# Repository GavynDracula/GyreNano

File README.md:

# Gyre Nano · 洄流

**English** | [简体中文](README.zh-CN.md)

A wireless, hot-swap split trackball keyboard enclosure derived from [BastardKB Charybdis Nano](https://github.com/Bastardkb/Charybdis). It keeps the familiar 3×5 keywell and thumb layout while replacing the open frame with a rounded, closed enclosure inspired by Charybdis MK2.

“Gyre / 洄流” echoes the swirling water of Charybdis; Nano denotes the compact layout. This is an independent derivative project.

**Current enclosure prototype: integrated raised shoulders and a rounded forward ball collar.** The latest upper shells preserve the original key/thumb/ball mounting relationships and reuse the existing bottom trays and FR4/FPC supports. Geometry and assembly-clearance checks have passed; these shells have not been sliced or physically assembled. Images show the current model.

[Latest models and checks](models/raised-rim/README.md) · [Ball-collar close-up](models/raised-rim/right-outer-seam.png) · [Top view](models/raised-rim/top.png)

## Layout and compatibility

- 3×5 main keys per half; three left thumb keys, two right thumb keys and a 34 mm trackball: 35 keys total.
- **Mounting positions and relative axes of the main keys, thumb keys and original trackball seat are preserved.** Baselines are mirrored Skeletyl V4 `case_v4_103.stl` on the left and Charybdis Nano `charybdisnano_v2_v187.stl` on the right. [Verification details](docs/geometry.md)
- The outer skin, thumb/ball transitions, sidewalls and bottom trays are redesigned. Height above the desk is not claimed identical to the original.
- Current electronics routes use FR4 or FPC keyfields, Kailh hot-swap sockets, header-mounted nrfmicro and ZMK. The original prototype used Amoeba Royale single-switch PCBs and Elite-C-holder; the new holder and support designs are linked below.
- Original holder mounting datums, a Type-C opening and bottom screw bosses adjacent to the sidewalls.
- Dedicated battery accommodation and a nice!view window remain planned. Ready-to-flash firmware is not included; the prototype PCB designs are linked below.

## Required prints

Print files are in [`models/`](models/) as **geometry-only 3MF**, in millimetres. Import at **100% scale** using your own printer profile; no printer settings or G-code are embedded. The left case is already mirrored.

| Part | File |
| --- | --- |
| Current right upper shell | [GyreNanoRightShell.3mf](models/raised-rim/GyreNanoRightShell.3mf) |
| Current left upper shell | [GyreNanoLeftShell.3mf](models/raised-rim/GyreNanoLeftShell.3mf) |
| Right bottom V7 | [gyre-nano-right-bottom-v7.3mf](models/3x5/gyre-nano-right-bottom-v7.3mf) |
| Left bottom V7 | [gyre-nano-left-bottom-v7.3mf](models/3x5/gyre-nano-left-bottom-v7.3mf) |
| FR4 supports, if using FR4 | [Main and thumb retainers](models/integrated-fr4/README.md) |
| FPC supports, if using FPC | [Direct supports and fit coupons](models/fpc-supports/README.md) |

Bottom STEP files are also in [`models/3x5/`](models/3x5/), in assembly coordinates; bottom 3MF files use bed coordinates. Upper cases are mesh models, without exact B-rep STEP exports.

Choose one support set for your PCB route. The earlier [V11/V7 shells](models/3x5/) and [V14 integrated shells](models/integrated-fr4/README.md) remain available as references. The current 3MFs preserve the checked STL coordinates and triangles exactly; large ASCII STL viewing copies remain local and are excluded from Git.

Use the original upstream trackball components below. Their final installed positions have been checked for static fit:

| Part | Charybdis file |
| --- | --- |
| Nano adapter top | [`adapter_v2_top_v75.stl`](https://github.com/Bastardkb/Charybdis/blob/47af70b9cd9b8d1d3a055ea88ab95c724bd3c02a/files/3x5%20nano/adapter_v2_top_v75.stl) |
| BTU adapter bottom | [`adapter_btu_bottom_v32.stl`](https://github.com/Bastardkb/Charybdis/blob/47af70b9cd9b8d1d3a055ea88ab95c724bd3c02a/files/mods/btu/adapter_btu_bottom_v32.stl) |
| Sensor cover | [`sensor_cover_v51.stl`](https://github.com/Bastardkb/Charybdis/blob/47af70b9cd9b8d1d3a055ea88ab95c724bd3c02a/files/sensor_cover_v51.stl) |

## FDM printing and assembly

Target trial printer: Creality K1C, 0.4 mm nozzle, PLA/PETG. Slice the current models using your own profile. Start with the support fit coupons for your PCB route; the [earlier holder/USB and ball/thumb samples](models/trials/) can check inherited interfaces but do not reproduce the new shoulder or collar. Keycap travel, tool access, adapter installation motion, support removal and manufacturing tolerances still need physical trials. Local thin features inherited from the ball opening are documented in the [current checks](models/raised-rim/README.md).

[FDM printing notes](docs/printing.md) · [Geometry checks and limits](docs/geometry.md) · [Build guide (TBD)](docs/build-guide.md)

## Electronics and integrated prints

**Electronics baseline: v0.2.0-prototype.1 — waiting for PCB samples and physical assembly.** The current enclosure update adds no PCB changes. Both column-PCB routes can use the latest upper shells with their matching supports; the earlier release archives retain their original models.

| Route / part | Files |
| --- | --- |
| FR4 keyfield, 0.6 mm, 99.70 × 99.80 mm | [V33 KiCad / EDA / Gerber](pcb/keyfield-fr4/README.md) |
| Retained electrically isolated FR4 alternative | [V32](pcb/keyfield-fr4/alternative-isolated/README.md) |
| FPC keyfield, 0.11 mm, 97.18 × 96.47 mm | [V27 KiCad / sample Gerber](pcb/keyfield-fpc/README.md) |
| Left/right controller holders | [Corrected native EDA projects](pcb/holders/README.md) |
| PMW3610 sensor with FFC | [Corrected native EDA project](pcb/sensor/README.md) |
| Current upper shells | [3MF / previews / checks](models/raised-rim/README.md) |
| Matching FR4 retainers and V14 reference shells | [STL / STEP](models/integrated-fr4/README.md) |
| Bare-FPC direct supports | [STL / 3MF / STEP](models/fpc-supports/README.md) |

Existing holder interfaces and key/ball mounting poses are retained. Six keyfield FFCs are still required per hand. Cross-region FR4 bridges must be removed before curved installation. Thin-FR4 forming, FPC durability, complete cable paths and printed fit remain trial items. No 0.4 mm thickness change is included.

[Electronics index](pcb/README.md) · [BOM](pcb/keyfield-fpc/BOM.zh-CN.md) · [CSV](pcb/keyfield-fpc/BOM.csv) · [All prints](models/README.md) · [Firmware placeholder](docs/firmware.md)

## Repository layout

| Path | Contents |
| --- | --- |
| `models/` | Print-ready geometry, integrated shells and FR4/FPC retainers |
| `pcb/` | Current KiCad/EDA projects, sample packages, BOM and checks |
| `docs/` | Build/printing notes, images, verification and release records |
| `development/` | Modeling sources, dimensions, reference geometry and engineering tools |

See [development notes](docs/DEVELOPMENT.md) for dependencies and coordinate conventions. Old cross-version pipelines are preserved as a checksummed engineering snapshot attached to the pre-release; disposable exports and local caches are excluded from Git.

## Attribution and license

Mechanical designs derive from [Charybdis](https://github.com/Bastardkb/Charybdis) and [Skeletyl](https://github.com/Bastardkb/Skeletyl) by BastardKB and their original contributors, under **CC BY-NC-SA 4.0**. Changes here include the closed skin, blended transitions, wireless hardware accommodation and matching bottom trays.

[Elite-C-holder](https://github.com/Bastardkb/Elite-C-holder), [Amoeba Royale](https://github.com/mtl/keyboard-pcbs/tree/master/amoeba-royale) and [ZMK](https://github.com/zmkfirmware/zmk) retain their respective authorship and licenses. See [license scope](LICENSE.md) and [source records](docs/ATTRIBUTION.md).

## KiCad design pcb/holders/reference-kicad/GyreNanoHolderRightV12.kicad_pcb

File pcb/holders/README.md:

# Left / right holders

The current editable designs are the corrected native JLCEDA V22 projects:

- [Left holder](eda/GyreNanoHolderLeft/GyreNanoHolderLeft.eprj3).
- [Right holder](eda/GyreNanoHolderRight/GyreNanoHolderRight.eprj3).

Keep each project folder intact. Each holder has seven 6-pin FFC sockets: J1–J5 main columns, J6 thumb, J7 sensor (unused on the left). The controller/header mounting datums and battery/switch interfaces are retained. Source stack thickness is 1.6 mm; the actual order selections are not independently verified.

[EDA validation and deliberate changes](../eda-validation/README.md) · [BOM](../keyfield-fpc/BOM.zh-CN.md)

`reference-kicad/` contains the original V12 source boards and a local footprint library. **These older boards omit controller PTH solder-mask openings that were corrected in EDA.** They are provenance references, not the recommended reorder source.

中文：左右 holder 用户已打板；当前入口为原生嘉立创 EDA 工程，每侧七个插座。参考 KiCad 版保留原始数据，但旧阻焊开窗问题没有回填，重新下单请使用 EDA 版。项目叠层厚度与实际订单参数应区分。

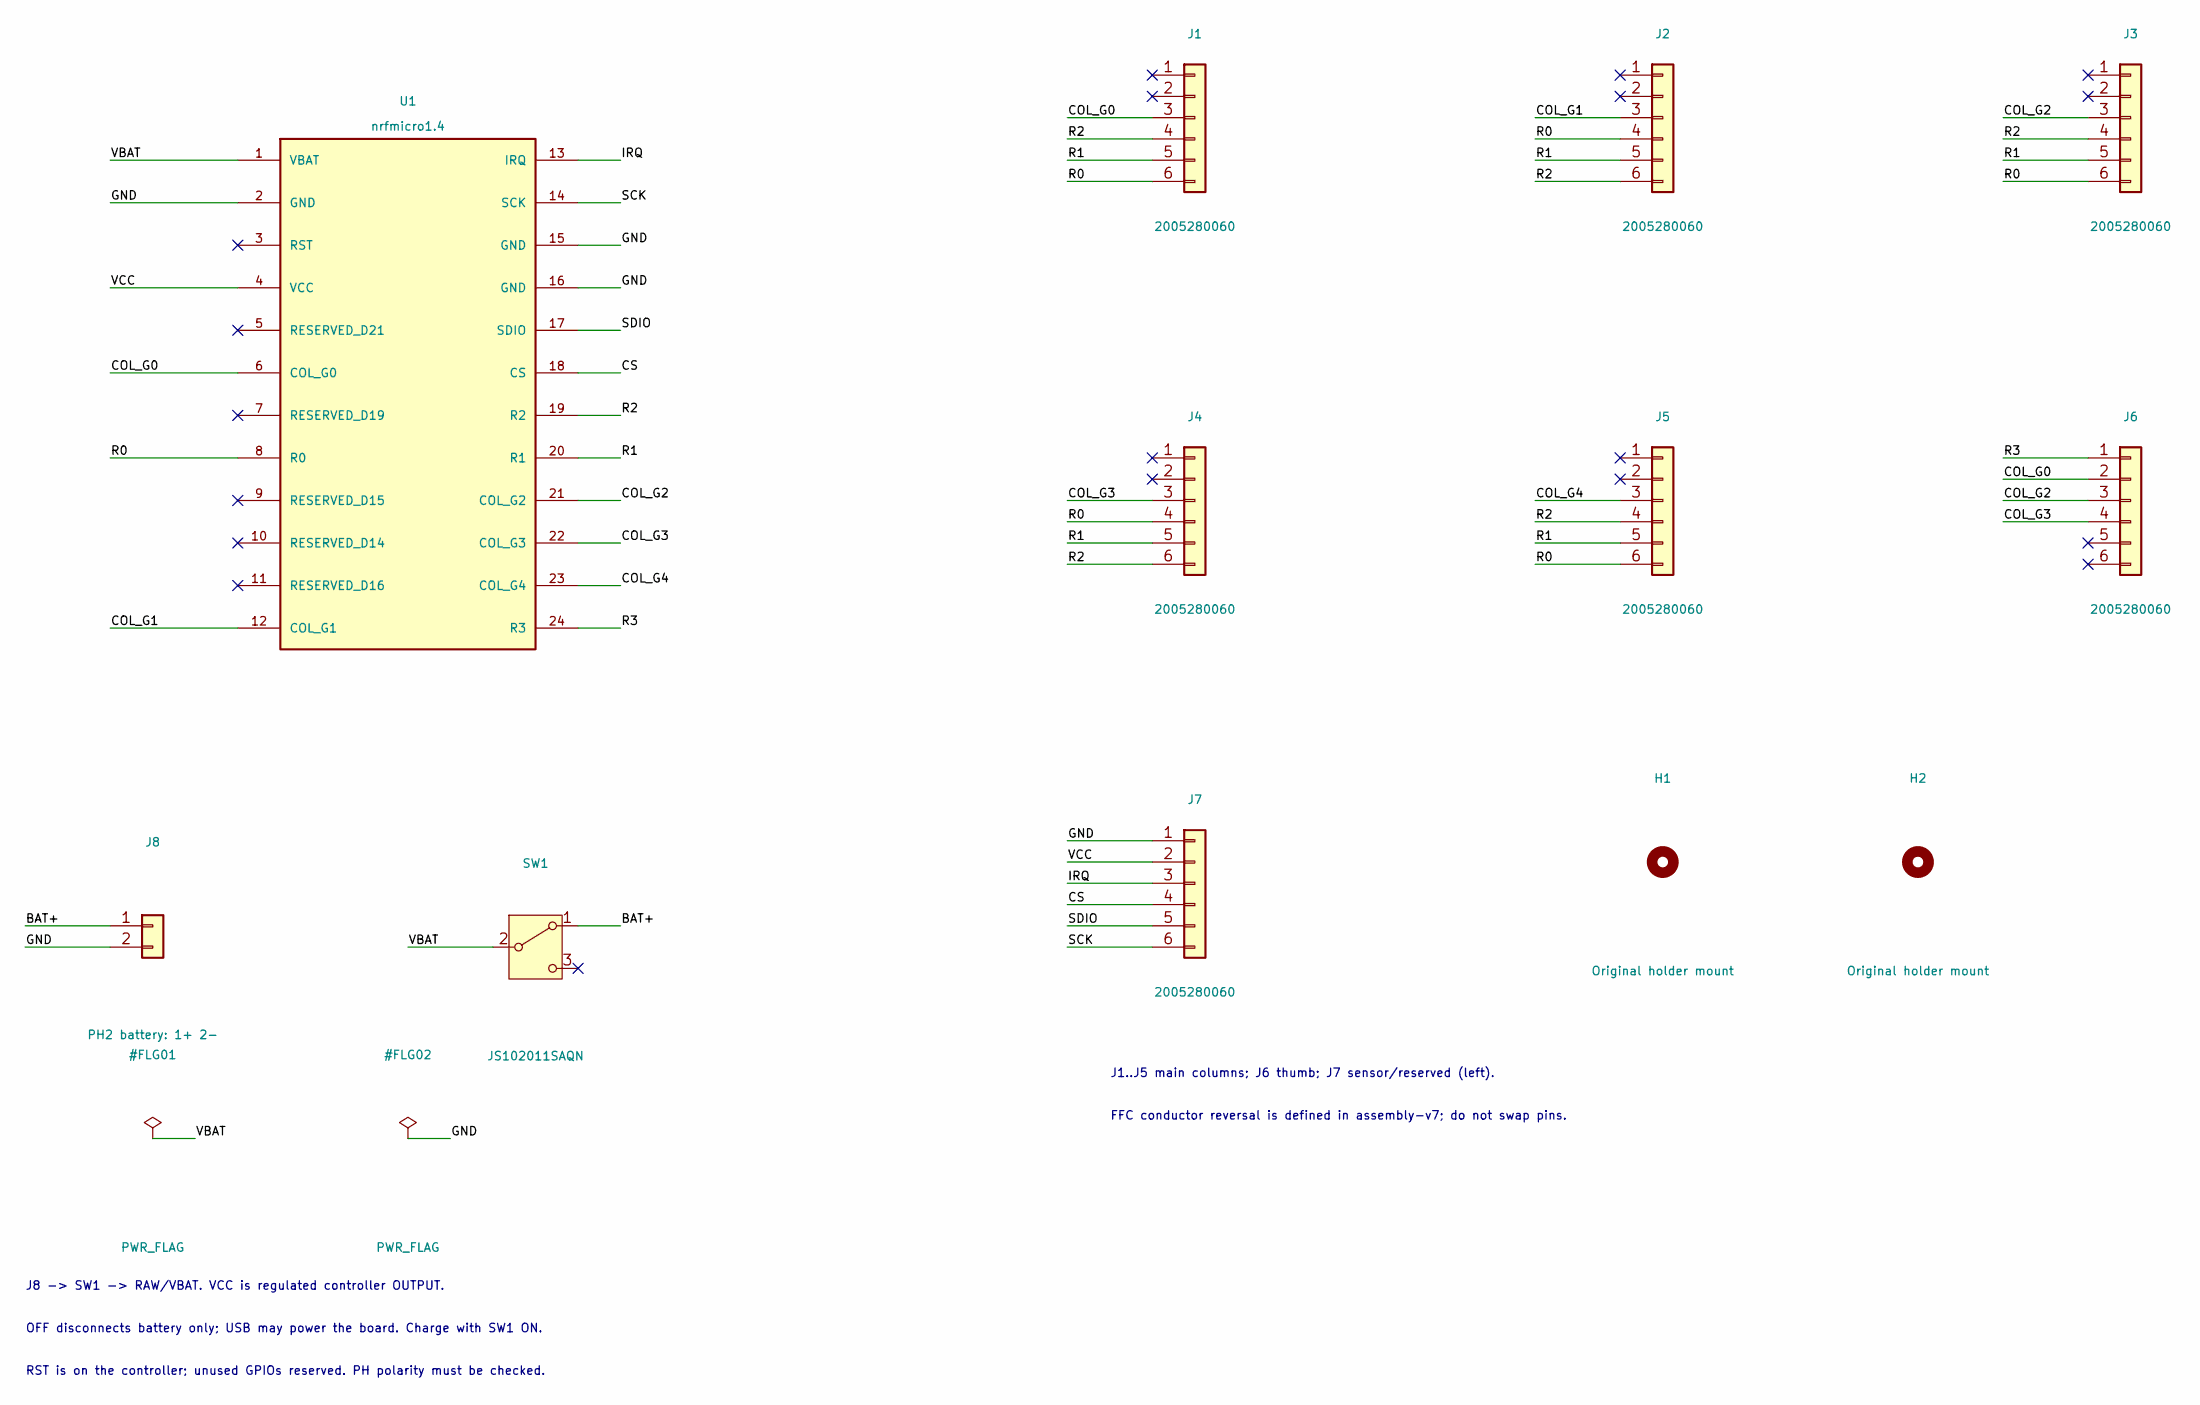
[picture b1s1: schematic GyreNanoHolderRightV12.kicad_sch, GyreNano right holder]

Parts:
H1, H2: Original holder mount; Mount4
J1: 2005280060; FFC6_right_J1
J2: 2005280060; FFC6_right_J2
J3: 2005280060; FFC6_right_J3
J4: 2005280060; FFC6_right_J4
J5: 2005280060; FFC6_right_J5
J6: 2005280060; Molex_200528-0060_1x06-1MP_P1.00mm_Horizontal
J7: 2005280060; FFC6_right_J7
J8: PH2 battery: 1+ 2-; JST_PH_B2B-PH-SM4-TB_1x02-1MP_P2.00mm_Vertical
SW1: JS102011SAQN; SW_SPDT_CK_JS102011SAQN
U1: nrfmicro1.4; Controller24_right

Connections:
/BAT+: J8.1, SW1.1 (A)
/COL_G0: J1.3, J6.2, U1.6 (COL_G0)
/COL_G1: J2.3, U1.12 (COL_G1)
/COL_G2: J3.3, J6.3, U1.21 (COL_G2)
/COL_G3: J4.3, J6.4, U1.22 (COL_G3)
/COL_G4: J5.3, U1.23 (COL_G4)
/CS: J7.4, U1.18 (CS)
/GND: J7.1, J8.2, U1.2 (GND), U1.15 (GND), U1.16 (GND)
/IRQ: J7.3, U1.13 (IRQ)
/R0: J1.6, J2.4, J3.6, J4.4, J5.6, U1.8 (R0)
/R1: J1.5, J2.5, J3.5, J4.5, J5.5, U1.20 (R1)
/R2: J1.4, J2.6, J3.4, J4.6, J5.4, U1.19 (R2)
/R3: J6.1, U1.24 (R3)
/SCK: J7.6, U1.14 (SCK)
/SDIO: J7.5, U1.17 (SDIO)
/VBAT: SW1.2 (B), U1.1 (VBAT)
/VCC: J7.2, U1.4 (VCC)

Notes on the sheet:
J1..J5 main columns; J6 thumb; J7 sensor/reserved (left).
FFC conductor reversal is defined in assembly-v7; do not swap pins.
J8 -> SW1 -> RAW/VBAT. VCC is regulated controller OUTPUT.
OFF disconnects battery only; USB may power the board. Charge with SW1 ON.
RST is on the controller; unused GPIOs reserved. PH polarity must be checked.

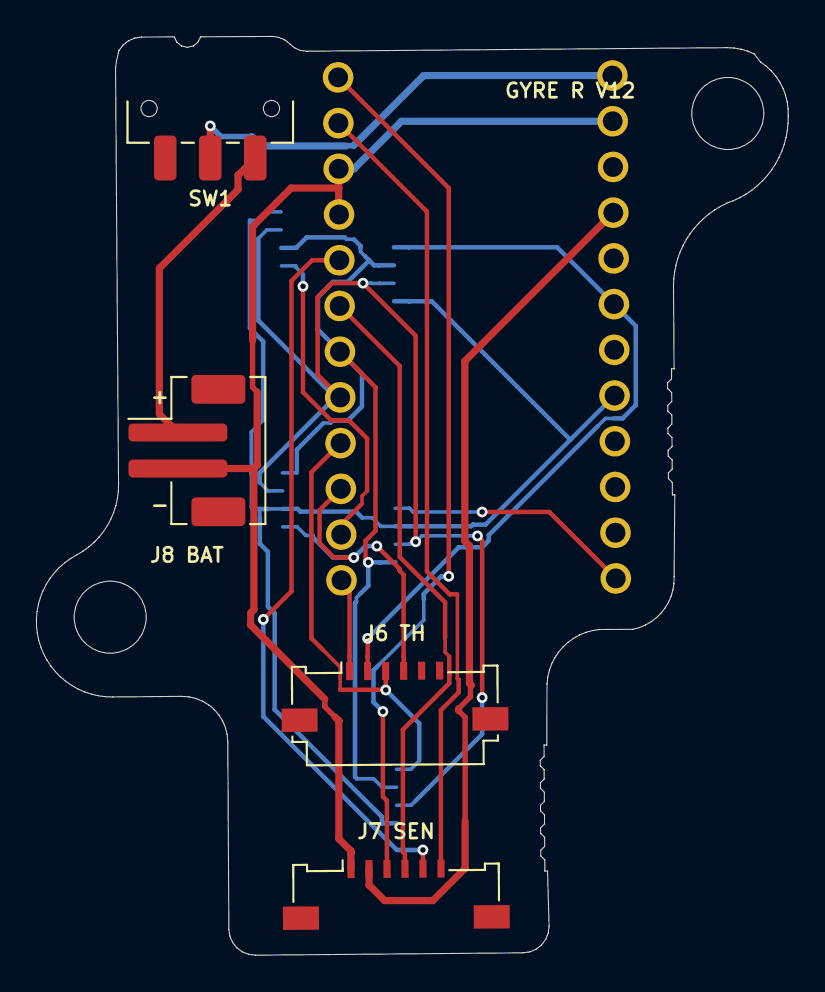
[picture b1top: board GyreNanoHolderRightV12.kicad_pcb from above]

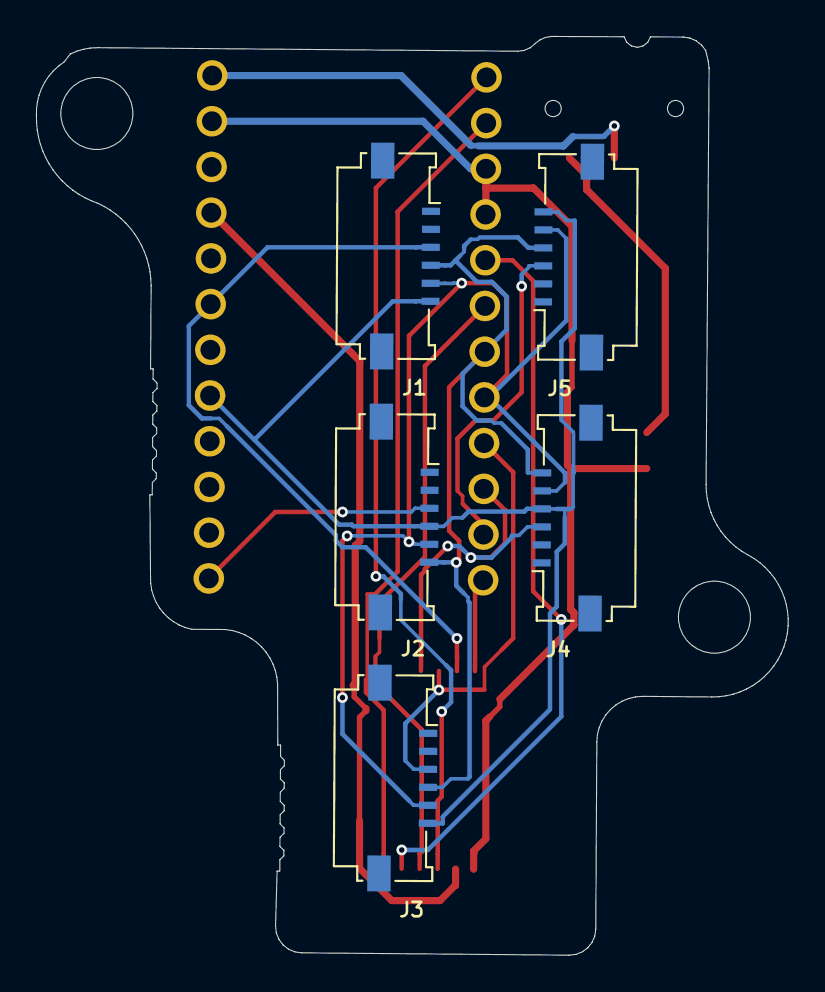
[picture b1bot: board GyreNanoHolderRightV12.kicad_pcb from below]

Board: 2 copper layers, 41.8 x 51.0 mm, 12 parts (5 on the bottom side), 17 nets.

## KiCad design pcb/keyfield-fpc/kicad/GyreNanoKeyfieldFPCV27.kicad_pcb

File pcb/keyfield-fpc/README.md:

# FPC keyfield — V27

[简体中文](README.zh-CN.md)

One common 18-key artwork for both hands; use 18 keys on the left and omit/remove T_SW1/T_D1 for 17 on the right. **97.176 × 96.472 mm**, two-layer **0.11 mm PI FPC**, 1/3 oz copper. Existing holder pin maps and six keyfield FFCs per hand are retained.

[KiCad project](kicad/GyreNanoKeyfieldFPCV27.kicad_pro) · [submitted sample ZIP](fabrication/GyreNanoKeyfieldFPCV27-SampleED.zip) · [sample process notes](SAMPLE-FABRICATION.txt) · [BOM CSV](BOM.csv) · [采购清单](BOM.zh-CN.md)

The sample package requests adhesiveless electrodeposited copper, yellow coverlay, ENIG 1 µin and no factory stiffeners. It is a material/assembly experiment, not a production-qualified specification. The older quotation ZIP remains separately named for traceability.

JP1: bridge 1–2 for left, 2–3 for right; never both. Remove optional inter-region bridges for the screened installation. [DRC/ERC, 64 cut/hand cases, CAM and folded geometry evidence](checks/) is retained unchanged.

The original sample notes describe separately bonded FR4 backers. An alternative [printed direct-support set](../../models/fpc-supports/README.md) is now available; it replaces those backers in its modeled stack. Do not stack both support schemes without a fit review. FPC bending, soldering, hot-swap loads and complete cable/latch assembly remain to be tested.

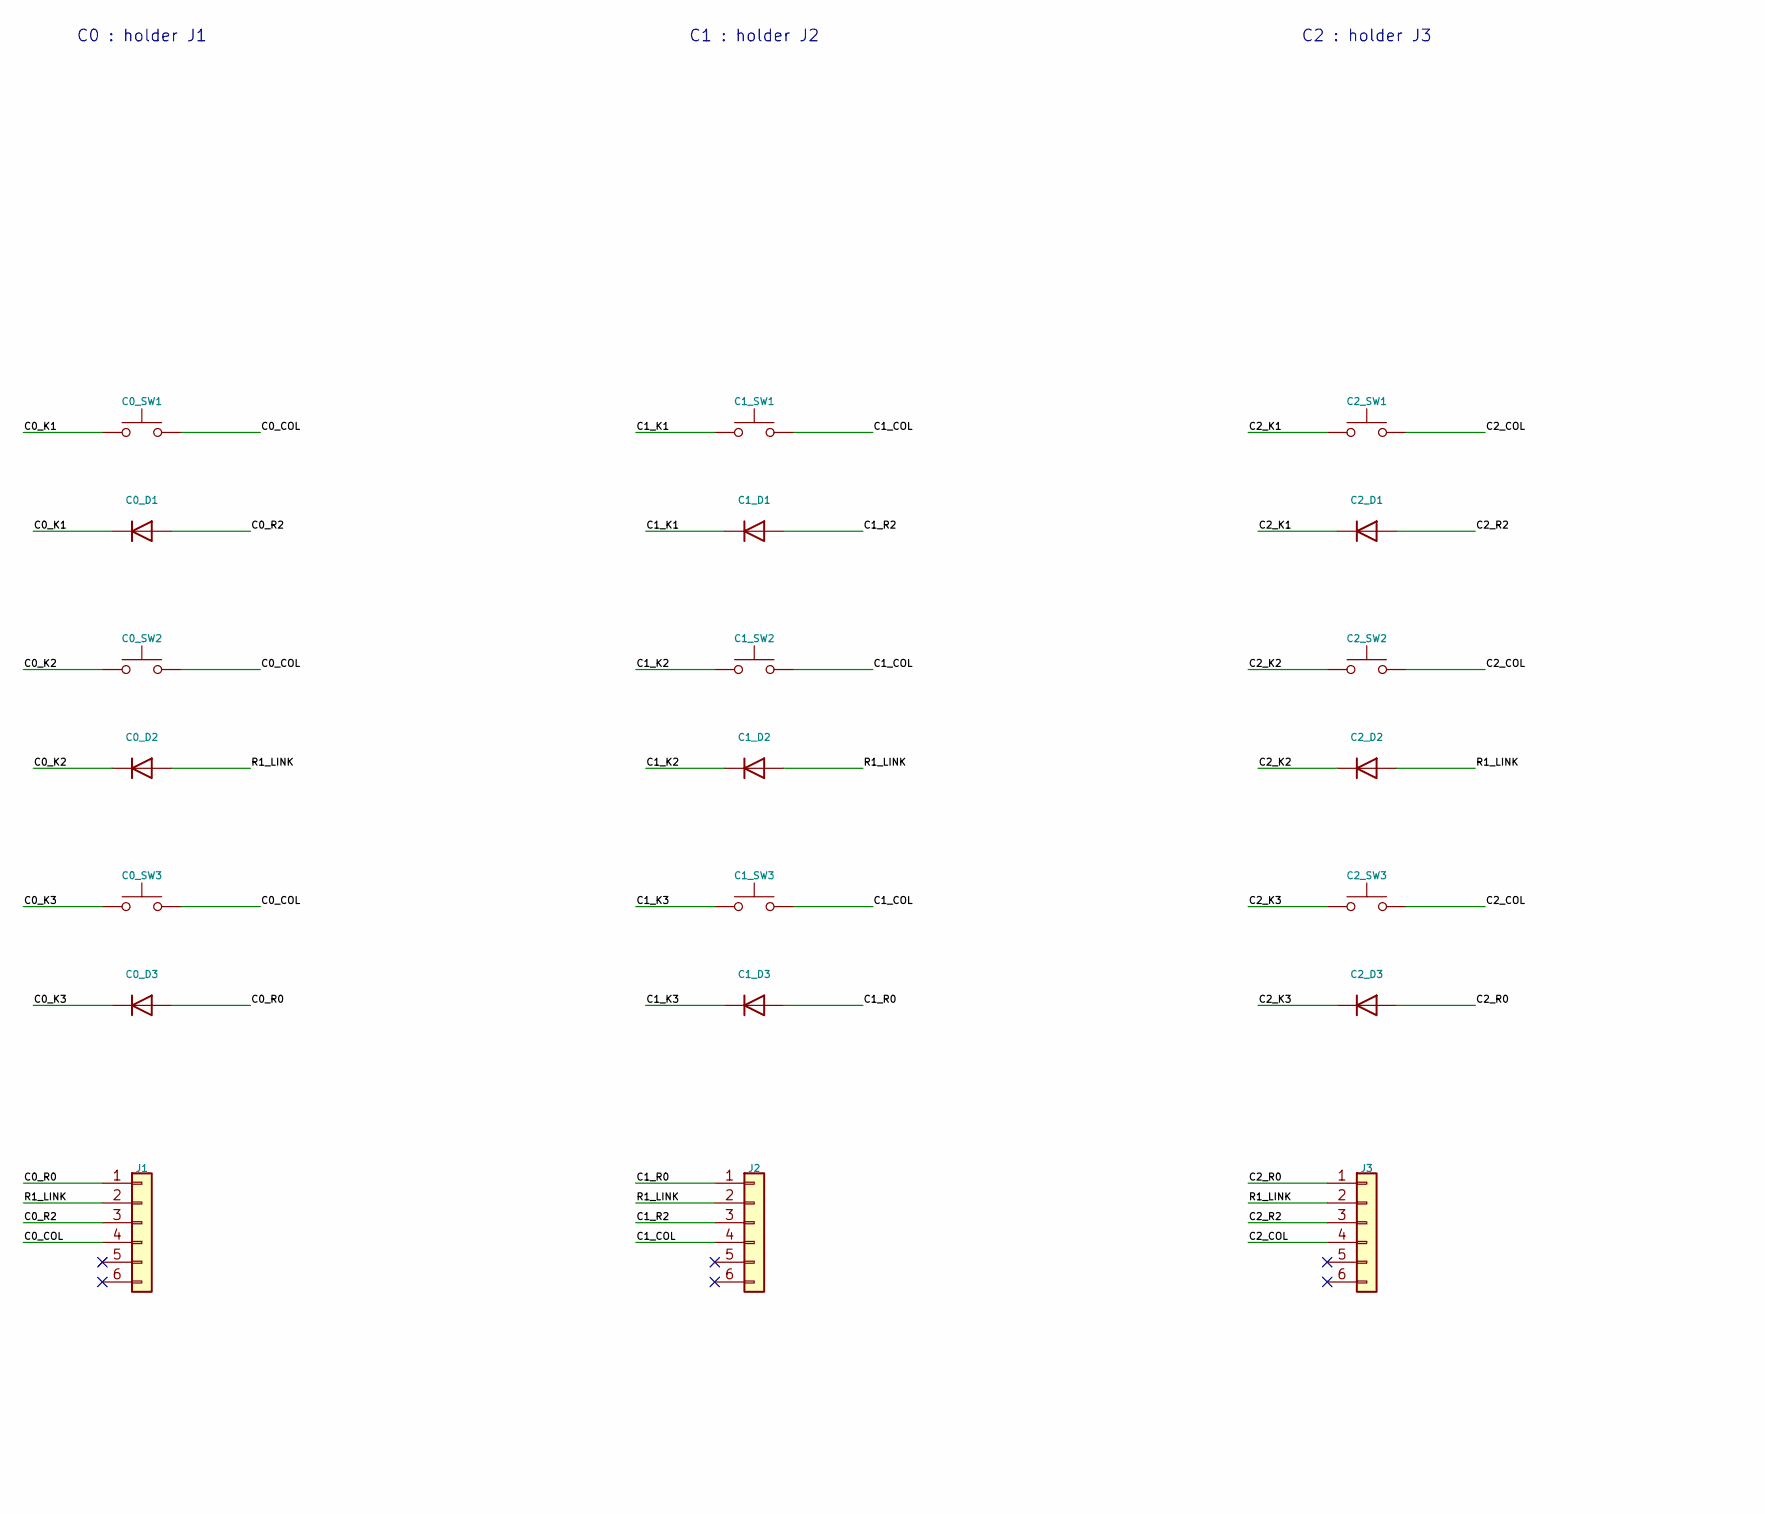
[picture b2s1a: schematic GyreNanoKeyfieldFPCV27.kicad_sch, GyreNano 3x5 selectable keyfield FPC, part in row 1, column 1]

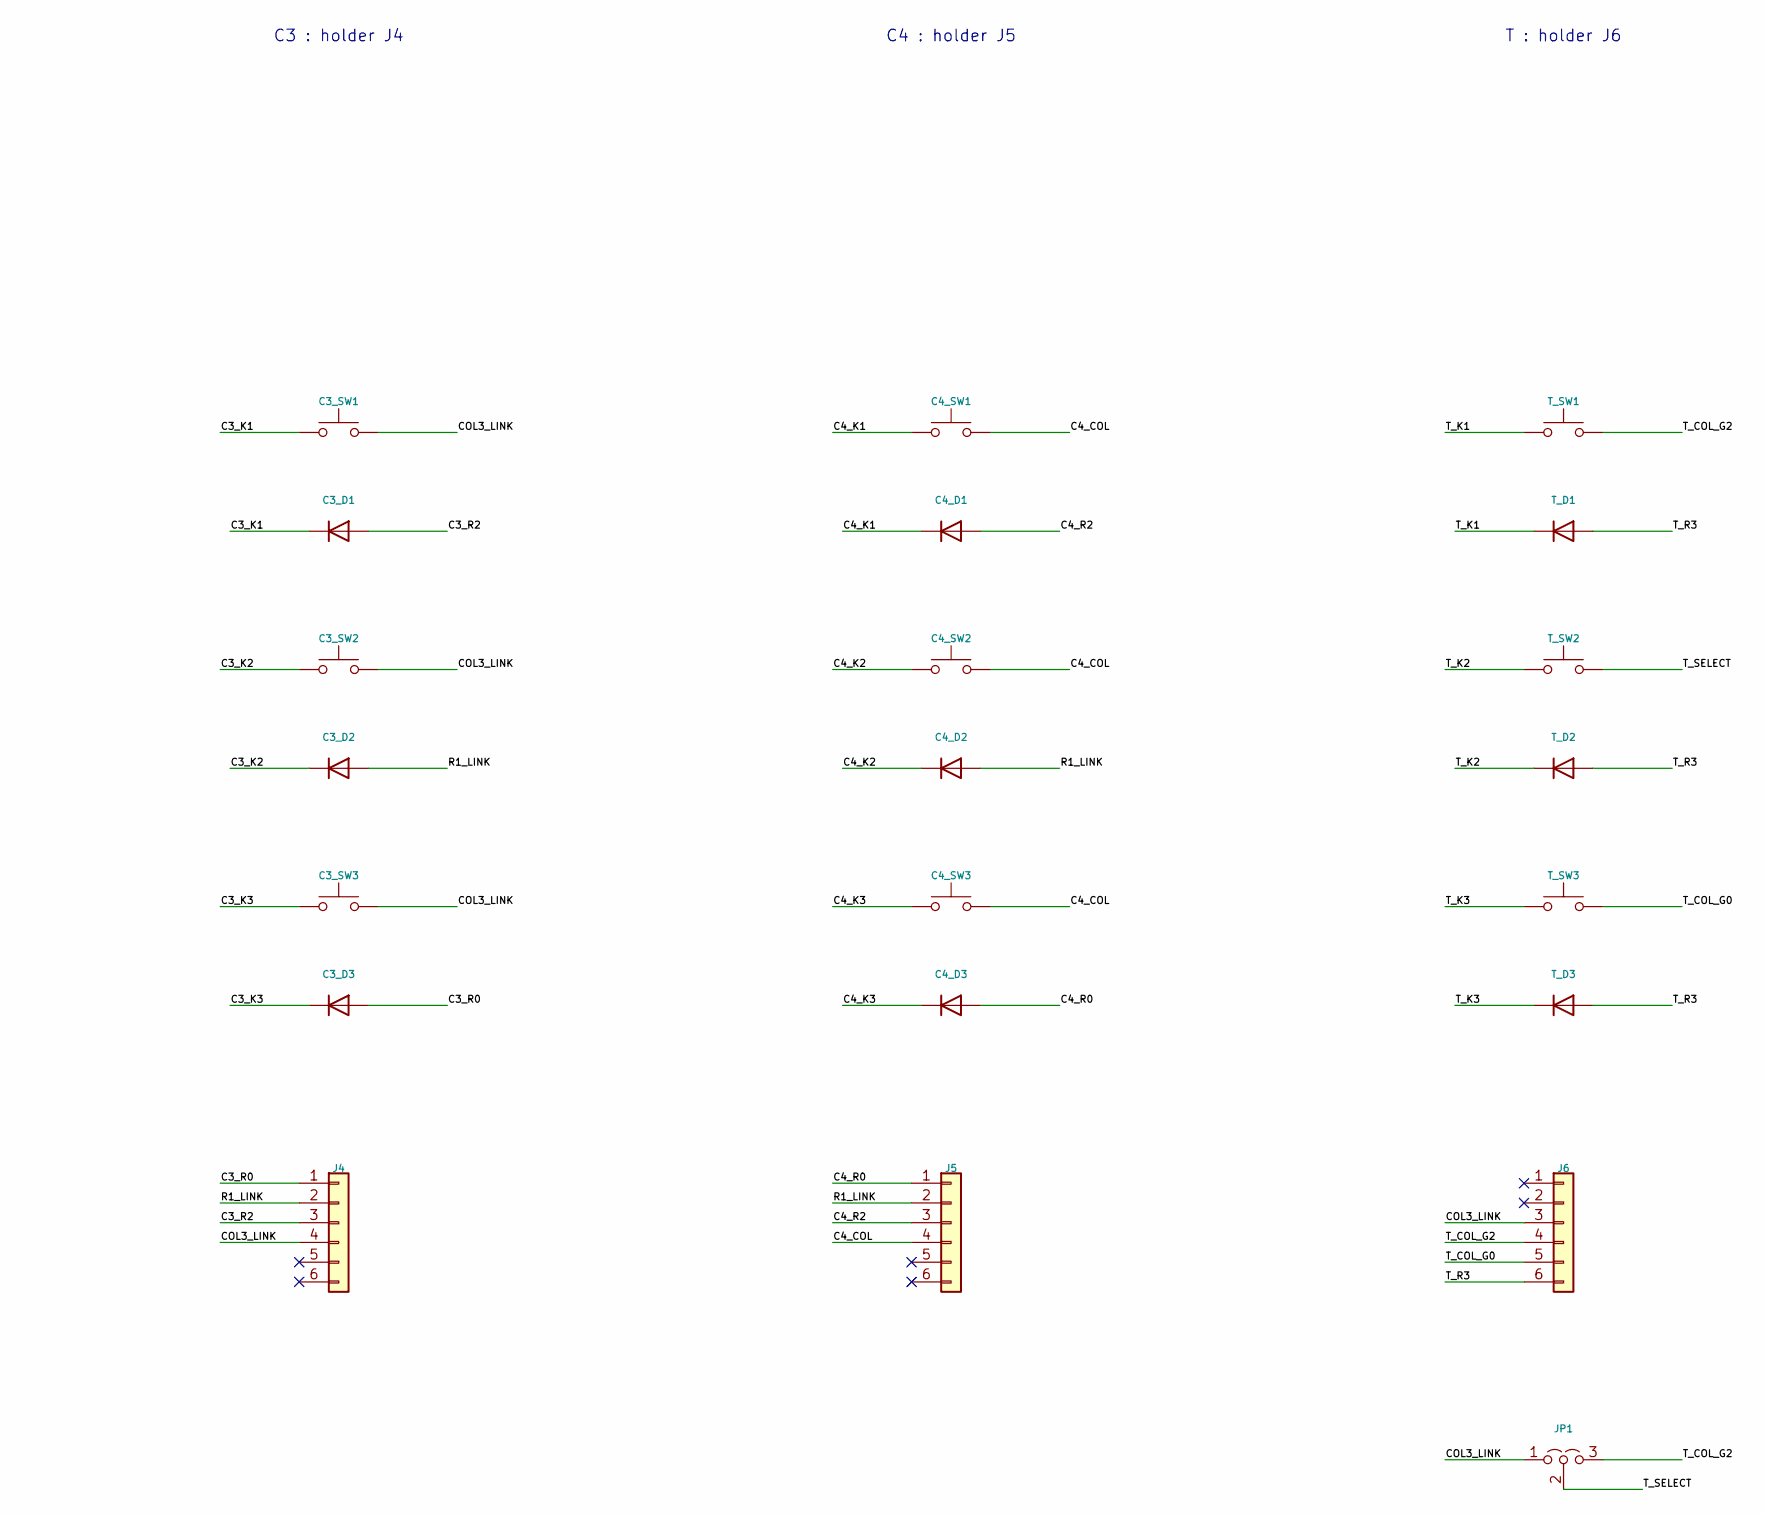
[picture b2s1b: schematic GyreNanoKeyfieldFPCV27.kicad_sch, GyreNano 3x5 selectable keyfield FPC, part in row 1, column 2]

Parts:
C0_D1: 1N4148W-7-F; D_C0_D1
C0_D2: 1N4148W-7-F; D_C0_D2
C0_D3: 1N4148W-7-F; D_C0_D3
C0_SW1: CPG151101S11-16; SW_C0_SW1
C0_SW2: CPG151101S11-16; SW_C0_SW2
C0_SW3: CPG151101S11-16; SW_C0_SW3
C1_D1: 1N4148W-7-F; D_C1_D1
C1_D2: 1N4148W-7-F; D_C1_D2
C1_D3: 1N4148W-7-F; D_C1_D3
C1_SW1: CPG151101S11-16; SW_C1_SW1
C1_SW2: CPG151101S11-16; SW_C1_SW2
C1_SW3: CPG151101S11-16; SW_C1_SW3
C2_D1: 1N4148W-7-F; D_C2_D1
C2_D2: 1N4148W-7-F; D_C2_D2
C2_D3: 1N4148W-7-F; D_C2_D3
C2_SW1: CPG151101S11-16; SW_C2_SW1
C2_SW2: CPG151101S11-16; SW_C2_SW2
C2_SW3: CPG151101S11-16; SW_C2_SW3
C3_D1: 1N4148W-7-F; D_C3_D1
C3_D2: 1N4148W-7-F; D_C3_D2
C3_D3: 1N4148W-7-F; D_C3_D3
C3_SW1: CPG151101S11-16; SW_C3_SW1
C3_SW2: CPG151101S11-16; SW_C3_SW2
C3_SW3: CPG151101S11-16; SW_C3_SW3
C4_D1: 1N4148W-7-F; D_C4_D1
C4_D2: 1N4148W-7-F; D_C4_D2
C4_D3: 1N4148W-7-F; D_C4_D3
C4_SW1: CPG151101S11-16; SW_C4_SW1
C4_SW2: CPG151101S11-16; SW_C4_SW2
C4_SW3: CPG151101S11-16; SW_C4_SW3
J1: 2005280060; Molex_1x06_J1
J2: 2005280060; Molex_1x06_J2
J3: 2005280060; Molex_1x06_J3
J4: 2005280060; Molex_1x06_J4
J5: 2005280060; Molex_1x06_J5
J6: 2005280060; Molex_1x06_J6
JP1: L:1-2 / R:2-3; Jumper_3_Open_JP1
T_D1: 1N4148W-7-F; D_T_D1
T_D2: 1N4148W-7-F; D_T_D2
T_D3: 1N4148W-7-F; D_T_D3
T_SW1: MX hot-swap; SW_T_SW1
T_SW2: MX hot-swap; SW_T_SW2
T_SW3: MX hot-swap; SW_T_SW3

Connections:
/C0_COL: C0_SW1.2, C0_SW2.2, C0_SW3.2, J1.4
/C0_K1: C0_D1.1 (K), C0_SW1.1
/C0_K2: C0_D2.1 (K), C0_SW2.1
/C0_K3: C0_D3.1 (K), C0_SW3.1
/C0_R0: C0_D3.2 (A), J1.1
/C0_R2: C0_D1.2 (A), J1.3
/C1_COL: C1_SW1.2, C1_SW2.2, C1_SW3.2, J2.4
/C1_K1: C1_D1.1 (K), C1_SW1.1
/C1_K2: C1_D2.1 (K), C1_SW2.1
/C1_K3: C1_D3.1 (K), C1_SW3.1
/C1_R0: C1_D3.2 (A), J2.1
/C1_R2: C1_D1.2 (A), J2.3
/C2_COL: C2_SW1.2, C2_SW2.2, C2_SW3.2, J3.4
/C2_K1: C2_D1.1 (K), C2_SW1.1
/C2_K2: C2_D2.1 (K), C2_SW2.1
/C2_K3: C2_D3.1 (K), C2_SW3.1
/C2_R0: C2_D3.2 (A), J3.1
/C2_R2: C2_D1.2 (A), J3.3
/C3_K1: C3_D1.1 (K), C3_SW1.1
/C3_K2: C3_D2.1 (K), C3_SW2.1
/C3_K3: C3_D3.1 (K), C3_SW3.1
/C3_R0: C3_D3.2 (A), J4.1
/C3_R2: C3_D1.2 (A), J4.3
/C4_COL: C4_SW1.2, C4_SW2.2, C4_SW3.2, J5.4
/C4_K1: C4_D1.1 (K), C4_SW1.1
/C4_K2: C4_D2.1 (K), C4_SW2.1
/C4_K3: C4_D3.1 (K), C4_SW3.1
/C4_R0: C4_D3.2 (A), J5.1
/C4_R2: C4_D1.2 (A), J5.3
/COL3_LINK: C3_SW1.2, C3_SW2.2, C3_SW3.2, J4.4, J6.3, JP1.1 (A)
/R1_LINK: C0_D2.2 (A), C1_D2.2 (A), C2_D2.2 (A), C3_D2.2 (A), C4_D2.2 (A), J1.2, J2.2, J3.2, J4.2, J5.2
/T_COL_G0: J6.5, T_SW3.2
/T_COL_G2: J6.4, JP1.3 (B), T_SW1.2
/T_K1: T_D1.1 (K), T_SW1.1
/T_K2: T_D2.1 (K), T_SW2.1
/T_K3: T_D3.1 (K), T_SW3.1
/T_R3: J6.6, T_D1.2 (A), T_D2.2 (A), T_D3.2 (A)
/T_SELECT: JP1.2 (C), T_SW2.2

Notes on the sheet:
C0 : holder J1
C1 : holder J2
C2 : holder J3
C3 : holder J4
C4 : holder J5
T : holder J6

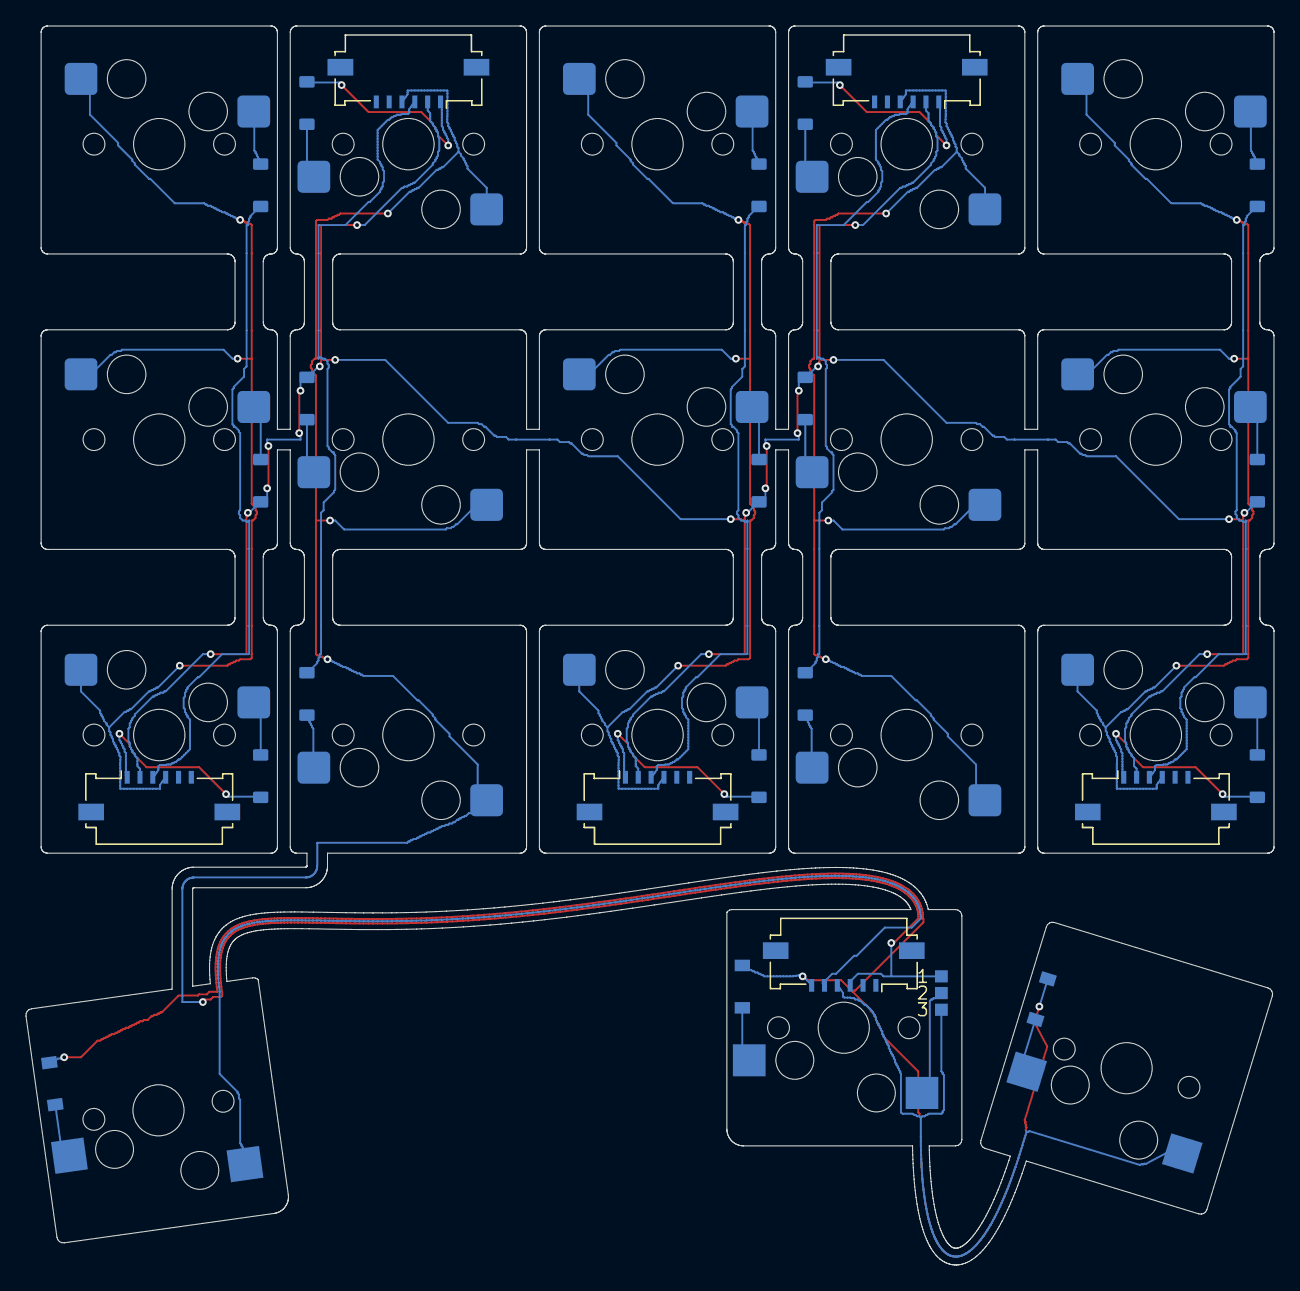
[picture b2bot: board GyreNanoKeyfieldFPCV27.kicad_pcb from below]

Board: 2 copper layers, 97.2 x 96.5 mm, 43 parts (43 on the bottom side), 38 nets.

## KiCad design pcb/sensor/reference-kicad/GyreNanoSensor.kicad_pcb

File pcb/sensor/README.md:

# PMW3610 FFC sensor

[Native JLCEDA project](eda/GyreNanoSensor/GyreNanoSensor.eprj3) · [validation](../eda-validation/README.md) · [BOM](../keyfield-fpc/BOM.zh-CN.md)

The six-wire interface is replaced with a Molex 2005280060 FFC socket. Sensor pins 1–6 are SCLK_2 / SDIO_2 / NCS_2 / MOTION_2 / VCC / GND; preserve the verified reversed conductor mapping to the right holder J7. Sensor VCC is not a direct battery input.

The native EDA V22 version corrects U2 PTH solder-mask openings and increases mounting-hole ground-copper clearance. The old V5 KiCad and upstream files remain in `reference-kicad/` and `upstream/` for provenance; do not use them as interchangeable manufacturing exports.

The source stack totals 1.29 mm, not a confirmed finished-thickness order. Optical stack, cover clamp, real screw engagement and the original 34 mm trackball assembly still require physical checking.

Based on [ufan/charybdis-pmw3610-breakout](https://github.com/ufan/charybdis-pmw3610-breakout) and [victorlucachi/charybdis-pmw3610-breakout](https://github.com/victorlucachi/charybdis-pmw3610-breakout). The user's original Gerber was identified as victorlucachi's 2023-05-12 release; historical commit/file evidence is preserved in the engineering snapshot. Upstream authorship and license terms are retained.

中文：当前使用修正过阻焊开窗的 EDA 工程；旧 KiCad 仅作来源参考。继续使用原版镜片、传感器盖和轨迹球结构，实物光学堆叠尚未重新验证。

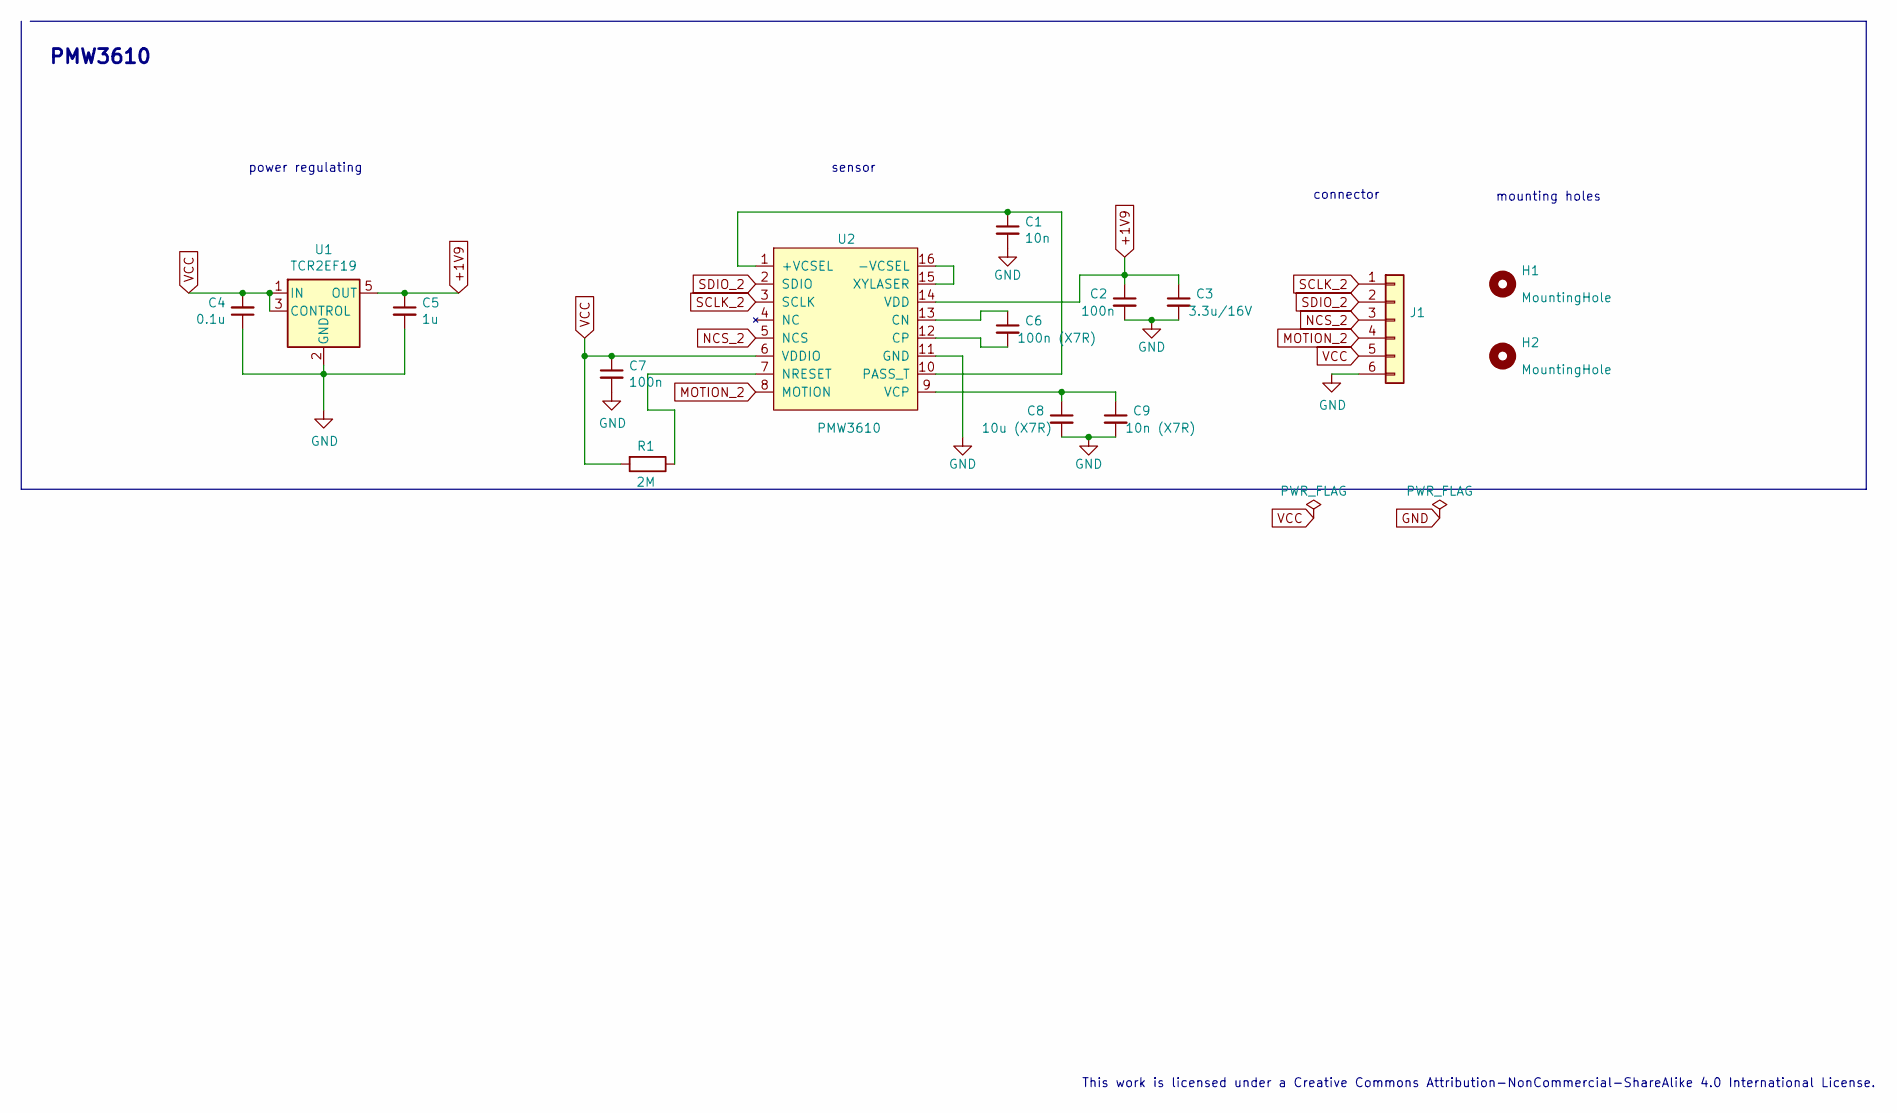
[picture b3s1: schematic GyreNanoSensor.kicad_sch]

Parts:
C1: 10n; C1_C_0603_1608Metric; LCSC C19666
C2: 100n; C2_C_0603_1608Metric; LCSC C19666
C3: 3.3u/16V; C3_C_0603_1608Metric; LCSC C19666
C4: 0.1u; C4_C_0603_1608Metric; LCSC C14663
C5: 1u; C5_C_0603_1608Metric; LCSC C15849
C6: 100n (X7R); C6_C_0603_1608Metric; LCSC C19666
C7: 100n; C7_C_0603_1608Metric; LCSC C19666
C8: 10u (X7R); C8_C_0603_1608Metric; LCSC C19666
C9: 10n (X7R); C9_C_0603_1608Metric; LCSC C19666
H1: MountingHole; H1_MountingHole_3.2mm_M3_ISO7380_Pad
H2: MountingHole; H2_
J1: 2005280060; Molex_200528-0060_1x06-1MP_P1.00mm_Horizontal
R1: 2M; R1_R_0603_1608Metric
U1: TCR2EF19; U1_SOT-23-5; LCSC C146366
U2: PMW3610; U2_PMW3610

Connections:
+1V9: C2.1, C3.1, C5.1, U1.5 (OUT), U2.14 (VDD)
GND: C1.2, C2.2, C3.2, C4.1, C5.2, C7.2, C8.2, C9.2, J1.6, U1.2 (GND), U2.11 (GND)
MOTION_2: J1.4, U2.8 (MOTION)
NCS_2: J1.3, U2.5 (NCS)
unnamed: C1.1, U2.1 (+VCSEL), U2.10 (PASS_T)
unnamed: U2.15 (XYLASER), U2.16 (-VCSEL)
unnamed: C6.1, U2.13 (CN)
unnamed: C6.2, U2.12 (CP)
unnamed: R1.1, U2.7 (NRESET)
unnamed: C8.1, C9.1, U2.9 (VCP)
SCLK_2: J1.1, U2.3 (SCLK)
SDIO_2: J1.2, U2.2 (SDIO)
VCC: C4.2, C7.1, J1.5, R1.2, U1.1 (IN), U1.3 (EN), U2.6 (VDDIO)

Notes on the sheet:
This work is licensed under a Creative Commons Attribution-NonCommercial-ShareAlike 4.0 International License.
sensor
PMW3610
power regulating
mounting holes
connector

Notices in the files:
pcb/sensor/reference-kicad/GyreNanoSensor.kicad_sch:
Copyright Quentin Lebastard
